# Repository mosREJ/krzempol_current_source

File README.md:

# Next to do
- [x] clear readmes 
- [ ] check diff btw 18 V and 20 V flyback (if I will be able to easily change output voltage) (https://webench.ti.com/power-designer/switching-regulator/customize/17?noparams=0)
- [ ] clear repo
- [ ] upgrade gitignore
- [ ] analyze voltages, currents and powers of flyback components

# TODO:
-    praca z wyprostowanym sieciowym: (230 * 1.41) + 100 V zapasu (max napięcie Uds mosfeta)
-    prąd do 10 A ciągłego (przy takim prądzie temp max 40 stC)
-    feedback prądu do MCU
-    MCU przez DAC (może pwm) zadaje prąd
-    zabezpieczenie, że jak DAC nie nadaje, to domyślnie możemy sobie wybrać np. zworką prąd max
-    układ do HW do odcinania powyżej prądu X
-    filtr 230 przed mostkiem
-    układy przeciwprzepięcieowe np. warystor
-    zapewne jakiś driver do mosfeta albo separacja galwaniczna, aby nie zabijało rasberki
     - albo dodatkowy pin odpala mosfeta, który odpala głównego mosfeta
- wykres mocy w zależnosci od warunków 
- update ltspice
- 2 uncjowa miedz -> kalkulator 
- dummy load electronics stack exchange
- projektowanie pcb pod optotranzystor 
- jakas blokada na pin od dac, aby np. przez jakis czas nie pluj 1
- zabzp temperaturowe 
- jakieś zabezpieczenie, że jak rasbar się wywali to piec powoli opada (duża stała RC + gpio które zawsze powinno podtzymywac)
- analiza temp + może jakieś pomiary
- jaka temp/watów bez radiatora ogarnie TO-92 220
- OPAMP rail to rail
- dlaczego nie można łączyć wejść https://electronics.stackexchange.com/questions/87780/driving-high-and-low-inputs-of-a-mosfet-driver-with-a-single-pwm-signal
- **większe footprinty jak lutujemy sami**

# TO LEARN/TODO 
- tns elektryka 
  - jak mierzyć oscylem/napięcie siecowe po wyprostowaniu (EEVblog)
- ogarnąć założenia projektowe np. opór minimalny 16 

# Problemy aktualnego rozwiazania:
- jak wygląda SSR w środku: https://www.youtube.com/watch?v=DxEhxjvifyY 

- jak w triak
       - przez to, że można odpalać traka w dowolnej fazie -> zakłócenia = może odpalać się za szybko/za wolno
       - dlatego używa się snubber circuit https://en.wikipedia.org/wiki/Snubber
       -?? czy my jesteśmy w stanie dać tyle miody na SSR przez pin od RPpico? -> ANS: chyba tak, bo optoizolacja to ogarnia, ale sprawdze dla sportu

**!!!!!!!!!!!!!!!!! POMIERZYC PIEC PODCZAS PRACY OSCYL, PRĄD NAPIĘCIA ITD , SOFT POD OSCYL ***************

# Ile prundu ze sterownika

I = dQ/dT 
e.g. 620 nC /

# Temp 
temp rosnie -> Vds rosnie 

- Pmosfety większa Rdson on
- ???? efekt millera?

# To watch:
- Mosfet losses https://www.youtube.com/watch?v=KSOHwVoxpzg&list=WL&index=9
- power losses mosfet https://www.youtube.com/watch?v=RViwOc4g-gw
- pcb tips: https://www.youtube.com/watch?v=kkc8BxL5Eo0&list=WL&index=11
- seperate trans: https://www.youtube.com/watch?v=3rvEdHyAd2k&list=WL&index=23
- thermal pcb design: https://www.youtube.com/watch?v=8v-wC5cM_Yk&list=WL&index=27
- EEV blog pcb review: https://www.youtube.com/watch?v=xhRhsCVF8mE&list=WL&index=30&pp=gAQBiAQB
- TVS: https://www.youtube.com/watch?v=MzxBBXpgwrE&list=WL&index=29
    - just blocks high volatege pulses and converts it to heat (small energy pulses)
    - more power: MOV -> metal oxide varistor
    - GDT Gas Discharge Tube **!! For high voltages +200 V** 
- passive filters: https://www.youtube.com/watch?v=NBLCqqmvy0A&list=WL&index=30
- miller effect: https://www.youtube.com/watch?v=w1PUG_8AsOc&list=WL&index=57
- flyback transformer: https://www.youtube.com/watch?v=VfSc15_XjiQ&list=WL&index=62
- opamp: https://www.youtube.com/watch?v=K03Rom3Cs28&list=WL&index=67&pp=gAQBiAQB
- 2 layers voltage regulator: https://www.youtube.com/watch?v=6AEUxY9QipI&list=WL&index=69&pp=gAQBiAQB
- main volatege + osciloscope: https://www.youtube.com/watch?v=LJ9CO5ViKPI&list=WL&index=70&pp=gAQBiAQB
- how power supply works: https://www.youtube.com/watch?v=cX4q0e124C4&list=WL&index=71&pp=gAQBiAQB
- moc bierna itd: https://www.youtube.com/watch?v=GnGLKBFcxMQ&list=WL&index=68&pp=gAQBiAQB
- ground planes: https://www.youtube.com/watch?v=BsOETPSszJQ&list=WL&index=72&pp=gAQBiAQB
- power planes/routing path: https://www.youtube.com/watch?v=lv8CZSc0o-c&list=WL&index=75&pp=gAQBiAQB
- via stiching: https://www.youtube.com/watch?v=TtSnG-Tl8yM&list=WL&index=74&pp=gAQBiAQB
- pcb ground: https://www.youtube.com/watch?v=Y-WhQ75Tqy4&list=WL&index=76&t=64s&pp=gAQBiAQB
- Feranec:
    - https://www.youtube.com/watch?v=icRzEZF3eZo&list=WL&index=78&pp=gAQBiAQB
    - https://www.youtube.com/watch?v=bU2Ef-2ZIK4&list=WL&index=79&pp=gAQBiAQB
    - https://www.youtube.com/watch?v=vzqZm2IFn6Y&list=WL&index=80&pp=gAQBiAQB
    - https://www.youtube.com/watch?v=vGq4uUtr6Uo&list=WL&index=81&pp=gAQBiAQB
    - https://www.youtube.com/watch?v=vALt6Sd9vlY&list=WL&index=82&pp=gAQBiAQB
    - https://www.youtube.com/watch?v=YounUJvIW04&list=WL&index=83&pp=gAQBiAQB
    - https://www.youtube.com/watch?v=_x2fzKEjUGQ&list=WL&index=84&t=1780s&pp=gAQBiAQB
    - https://www.youtube.com/watch?v=fJCRrEf_IH8&list=WL&index=85&pp=gAQBiAQB
    - https://www.youtube.com/watch?v=qVREULDBtjk&list=WL&index=86&pp=gAQBiAQB
    - https://www.youtube.com/watch?v=fkNa-FejWsQ&list=WL&index=87&pp=gAQBiAQB
    - https://www.youtube.com/watch?v=gHF5JyJF-N4&list=WL&index=88&pp=gAQBiAQB
    - https://www.youtube.com/watch?v=H2eQc4DxK30&list=WL&index=89&pp=gAQBiAQB
    - https://www.youtube.com/watch?v=9lgoL0C7PFc&list=WL&index=90&pp=gAQBiAQB
    - https://www.youtube.com/watch?v=yHn-XOcvJOY&list=WL&index=91&pp=gAQBiAQB
    - https://www.youtube.com/watch?v=2hvMgG6tKdg&list=WL&index=92&pp=gAQBiAQB
    - https://www.youtube.com/watch?v=3L8SaMZxpDw&list=WL&index=93&pp=gAQBiAQB
    - https://www.youtube.com/watch?v=vrt3lL5gEb0&list=WL&index=94&pp=gAQBiAQB
    - https://www.youtube.com/watch?v=kdCJxdR7L_I&list=WL&index=95&pp=gAQBiAQB
    - https://www.youtube.com/watch?v=hNHTwpegFBw&list=WL&index=97&t=5304s&pp=gAQBiAQB
    - https://www.youtube.com/watch?v=j2YGHZG1bLY&list=WL&index=98&t=1299s&pp=gAQBiAQB
    - QFN layout: https://www.youtube.com/watch?v=PsyK1BXdclQ&list=WL&index=99&pp=gAQBiAQB
    - https://www.youtube.com/watch?v=52fxuRGifLU&list=WL&index=100&pp=gAQBiAQB
- heatsink: https://www.youtube.com/watch?v=8ruFVmxf0zs&list=WL&index=101&pp=gAQBiAQB
- emi filters: https://www.youtube.com/watch?v=ABd5O7NJLr0&list=WL&index=105&pp=gAQBiAQB
- parallel mosfets: https://www.youtube.com/watch?v=AOf-i2vLd2o&list=WL&index=107&pp=gAQBiAQB
- design review: https://www.youtube.com/watch?v=eZnyBt2LVoc&list=WL&index=124&pp=gAQBiAQB 
- pcb stackup: https://www.youtube.com/watch?v=QAOEtfvCaMw&list=WL&index=129&pp=gAQBiAQB
- circuit protection: https://www.youtube.com/watch?v=GkXqE4x5Y3A&list=WL&index=132&pp=gAQBiAQB
- pcb options: https://www.youtube.com/watch?v=mT2Vp3HcIP4&list=WL&index=140&pp=gAQBiAQB
- layout fundamentals: https://www.youtube.com/watch?v=HTywk_tlcAk&list=WL&index=142&t=560s&pp=gAQBiAQB
- review deep dive: https://www.youtube.com/watch?v=FztXQ2UwllQ&list=WL&index=144&t=228s&pp=gAQBiAQB
- gate driver: https://www.youtube.com/watch?v=up0lIpZP8cI&list=WL&index=147&pp=gAQBiAQB
- skin effect: https://www.youtube.com/watch?v=FoHD_sW9SiI&list=WL&index=160&pp=gAQBiAQB
- induction satureation: https://www.youtube.com/watch?v=Tl_LH--5Ce8&list=WL&index=158&pp=gAQBiAQB
- proper scope: https://www.youtube.com/watch?v=JTfzgeJYFo8&list=WL&index=165&pp=gAQBiAQB
- power pcb design: https://www.youtube.com/watch?v=56p3_aORiJ0&list=WL&index=179&pp=gAQBiAQB
- how to learn pcb: https://www.youtube.com/watch?v=aODkA2mrimQ&list=WL&index=169&pp=gAQBiAQB
- fft ltspice: https://www.youtube.com/watch?v=rVAvW1Jh2AE&list=WL&index=168&pp=gAQBiAQB
- flyback: https://www.youtube.com/watch?v=-72g1V6v0GQ&list=WL&index=116&pp=gAQBiAQB
- optocoupler: https://www.youtube.com/watch?v=fW0pyb8X0RA&list=WL&index=112&pp=gAQBiAQB
- mosfets parraler: https://www.youtube.com/watch?v=AOf-i2vLd2o&list=WL&index=107&pp=gAQBiAQB
- perferct ppower supply: https://www.youtube.com/watch?v=zf-pvHysroM&list=WL&index=96&pp=gAQBiAQB
- cuuretn: https://www.youtube.com/watch?v=vrt3lL5gEb0&list=WL&index=94&pp=gAQBiAQB
- decouplong caps: https://www.youtube.com/watch?v=u40kX1DYKdA&list=WL&index=184&pp=gAQBiAQB
- mosfet: https://www.youtube.com/watch?v=AwRJsze_9m4&list=WL&index=198&pp=gAQBiAQB
- bypass cap: https://www.youtube.com/watch?v=BcJ6UdDx1vg&list=WL&index=202&pp=gAQBiAQB
- orignal of electronics: https://www.youtube.com/watch?v=FLaTU-t1CQM&list=WL&index=219&pp=gAQBiAQB

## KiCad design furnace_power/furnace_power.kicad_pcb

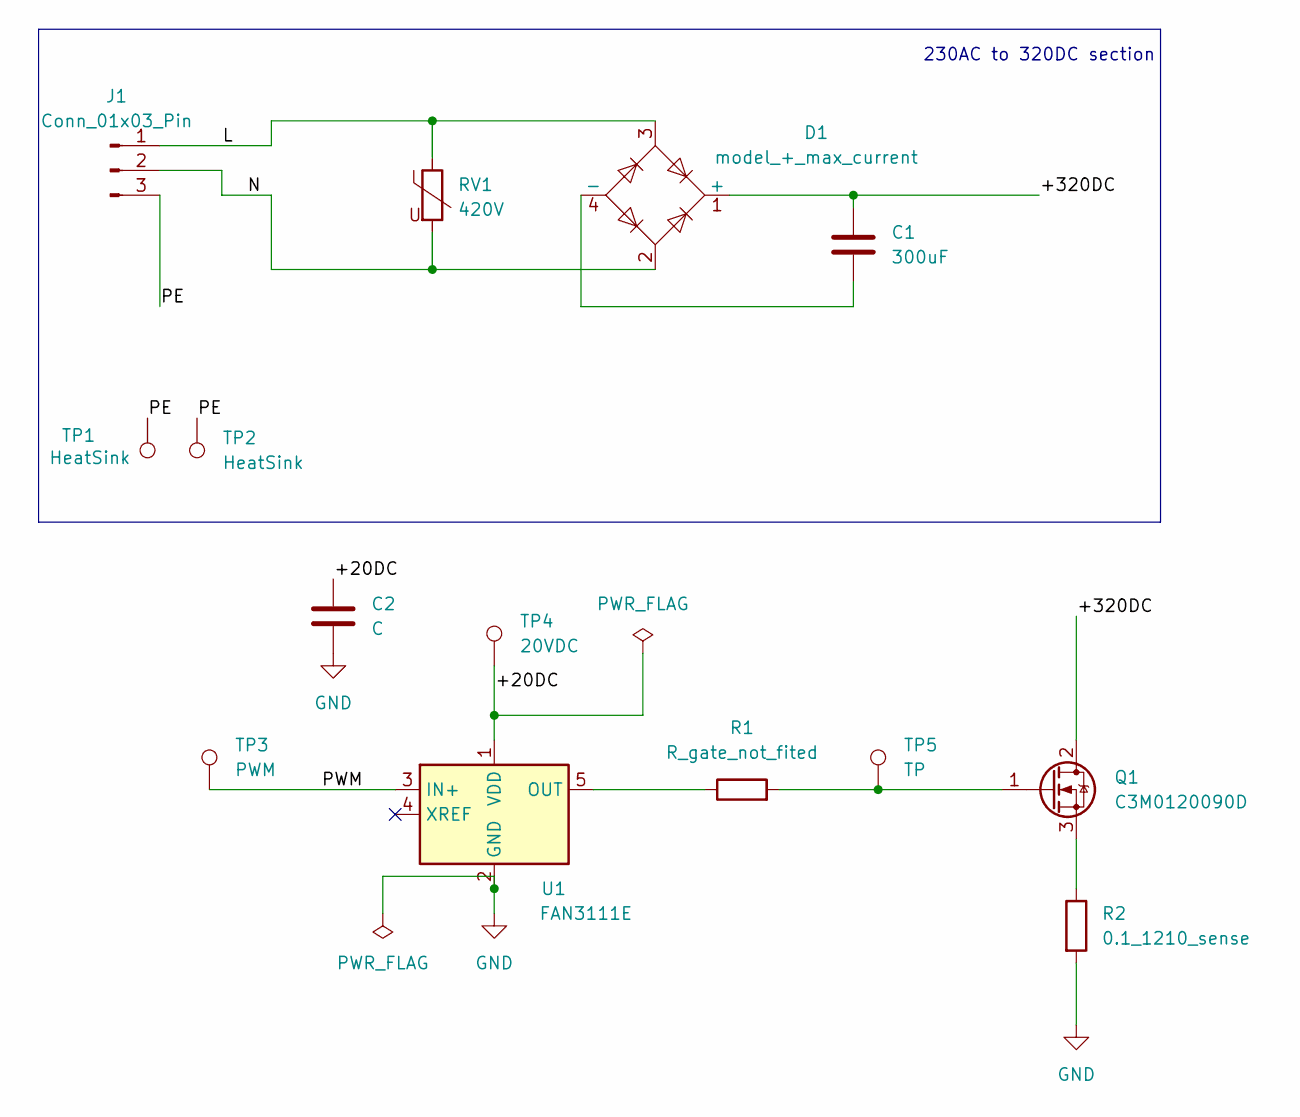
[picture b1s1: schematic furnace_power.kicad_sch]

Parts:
C1: 300uF; CP_Radial_D13.0mm_P7.50mm
C2: C; C_0603_1608Metric_Pad1.08x0.95mm_HandSolder
D1: model_+_max_current; Diode_Bridge_Vishay_KBU
J1: Conn_01x03_Pin; PhoenixContact_MCV_1,5_3-G-3.81_1x03_P3.81mm_Vertical
Q1: C3M0120090D; TO-247-3_Vertical
R1: R_gate_not_fited; R_0603_1608Metric_Pad0.98x0.95mm_HandSolder
R2: 0.1_1210_sense; R_1210_3225Metric
RV1: 420V; RV_Disc_D7mm_W5.7mm_P5mm
TP1, TP2: HeatSink; Pin_D1.3mm_L11.0mm_LooseFit
TP3: PWM; Pin_D1.3mm_L11.0mm_LooseFit
TP4: 20VDC; Pin_D1.3mm_L11.0mm_LooseFit
TP5: TP; Pin_D1.3mm_L11.0mm_LooseFit
U1: FAN3111E; SOT-23-5

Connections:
/+20DC: C2.1, TP4.1, U1.1 (VDD)
/+320DC: C1.1, D1.1 (+), Q1.2 (D)
/L: D1.3, J1.1, RV1.1
/N: D1.2, J1.2, RV1.2
/PE: J1.3, TP1.1, TP2.1
/PWM: TP3.1, U1.3 (IN+)
GND: C2.2, R2.2, U1.2 (GND)
unnamed: C1.2, D1.4 (-)
unnamed: Q1.1 (G), R1.2, TP5.1
unnamed: Q1.3 (S), R2.1
unnamed: R1.1, U1.5 (OUT)

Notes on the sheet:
230AC to 320DC section

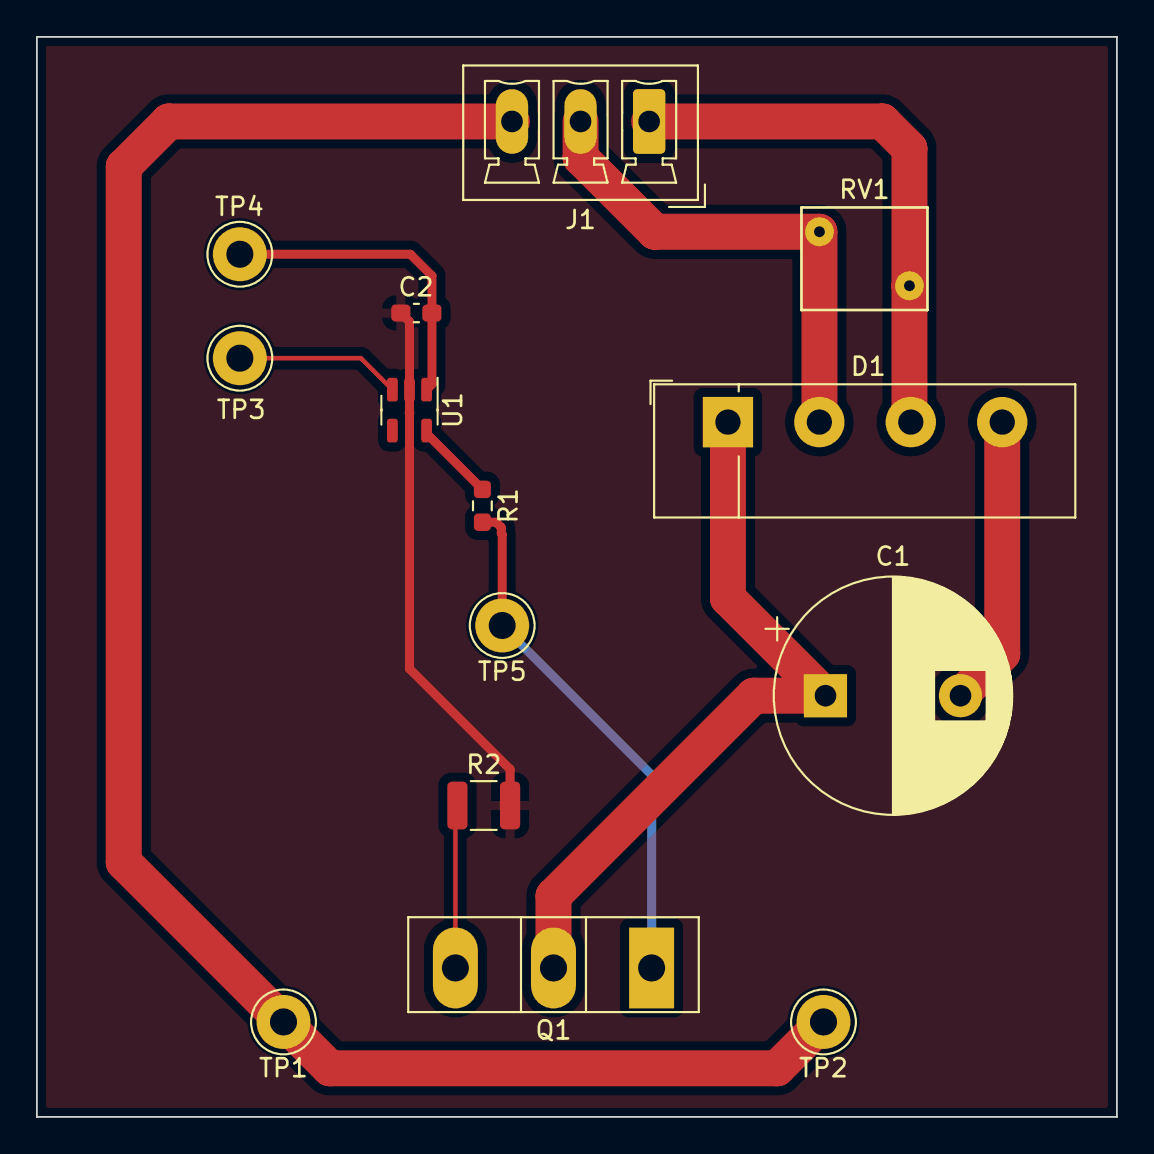
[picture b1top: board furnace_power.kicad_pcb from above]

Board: 2 copper layers, 60.0 x 60.0 mm, 14 parts (0 on the bottom side), 11 nets.

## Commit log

2024-02-21 init + first notes
2024-02-25 RADME update. Added results of prototype measurements
2024-02-26 Added ltspice impuls analyze file.
2024-03-02 Added symulation for present furnace setup. Added ltspice lib for triac.
2024-03-03 03.03.24 update notes
2024-03-09 Kicad init.
2024-03-11 Init of explanation of problem with furnace.
2024-03-24 Started main schematic.
2024-03-29 sync
2024-05-02 repo cleaning
2024-05-02 schematic of flyback v1
2024-06-15 idk the changes. Moving from omen to TB
